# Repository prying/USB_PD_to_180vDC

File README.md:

View this project on [CADLAB.io](https://cadlab.io/project/23945). 

# USB_PD_to_180vDC
uses usb power delivery to get a higher voltage and then steps it up to 180v for nixie tubes

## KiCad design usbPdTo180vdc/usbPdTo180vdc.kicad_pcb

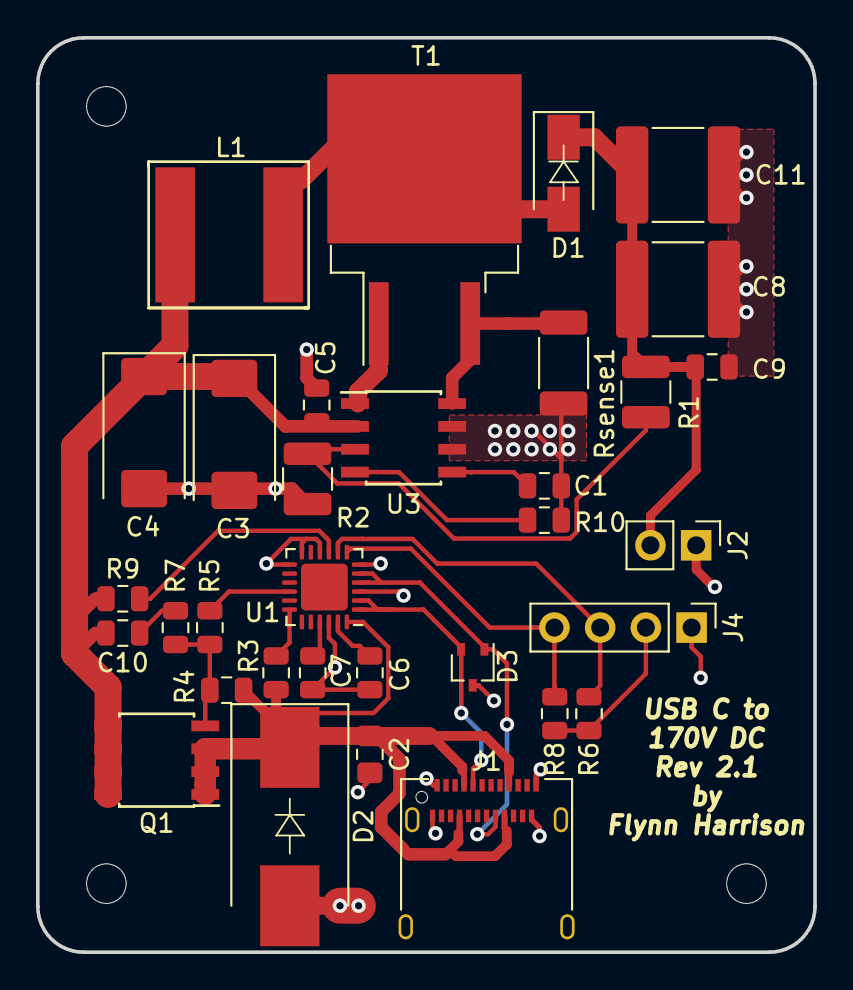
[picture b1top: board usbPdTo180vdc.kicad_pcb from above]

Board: 2 copper layers, 43.2 x 50.8 mm, 33 parts (0 on the bottom side), 22 nets.

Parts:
C1, C5, C9, C10: 0.1uF; C_0805_2012Metric
C2: 4.7uF; C_0805_2012Metric_Pad1.15x1.40mm_HandSolder
C3: 10uF; CP_EIA-7343-30_AVX-N
C4: 100uf; CP_EIA-7343-30_AVX-N
C6, C7: 1uF; C_0805_2012Metric
C8, C11: 2.2uF; C_2220_5650Metric
D1: ES2F; D_SMA
D2: SM15T; D_SMC_Handsoldering
D3: ESDA25W; SOT-323_SC-70
J1: 12401610E4_2A; USB_C_Receptacle_Amphenol_12401610E4-2A
J2: CONN_02; PinHeader_1x02_P2.54mm_Vertical
J4: QWIIC_CONNECTORJS-1MM; PinHeader_1x04_P2.54mm_Vertical
L1: 100uH; ASPI-8040S-101M-TCT-ND SMD
Q1: STS6P3LLH6; SOIC-8_3.9x4.9mm_P1.27mm
R1: 1M5; R_1210_3225Metric
R2: 12.7k; R_1210_3225Metric
R3, R9: 1K; R_0805_2012Metric
R4: 100K; R_0805_2012Metric
R5: 22K; R_0805_2012Metric
R6, R8: 2.2k; R_0805_2012Metric
R7: 100; R_0805_2012Metric
R10: 0; R_0805_2012Metric
Rsense1: 0R100; R_2010_5025Metric
T1: IRF644S; TO-263-2
U1: STUSB4500QTR; QFN-24-1EP_4x4mm_P0.5mm_EP2.6x2.6mm
U3: MAX1771ESA; SOIC-8_3.9x4.9mm_P1.27mm

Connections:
+3V3: J4.2, R6.1, R8.1
+15V: C3.1, C4.1, C5.1, C10.2, L1.1, Q1.5, Q1.6, Q1.7, Q1.8, R9.1, U3.2
GND: C1.2, C2.2, C3.2, C4.2, C5.2, C6.2, C7.2, C8.2, C9.2, C11.2, D2.2, D3.3, J1.A1, J1.A12, J1.B1, J1.B12, J2.1, J4.1, R2.2, R10.2, Rsense1.2, U1.3, U1.6, U1.10, U1.12, U1.13, U1.22, U3.6, U3.7
HV+: C8.1, C9.1, C11.1, D1.1, J2.2, R1.1
unnamed: C1.1, U3.5
unnamed: C6.1, U1.23
unnamed: C7.1, U1.21
unnamed: C10.1, R7.2
unnamed: D1.2, L1.2, T1.2
unnamed: D3.1, J1.B5, U1.4, U1.5
unnamed: D3.2, J1.A5, U1.1, U1.2
unnamed: Q1.4, R4.2, R5.1, R7.1
unnamed: R1.2, R2.1, U3.3
unnamed: R3.2, U1.18
unnamed: R5.2, U1.16
unnamed: R9.2, U1.9
unnamed: R10.1, U3.4
unnamed: Rsense1.1, T1.3, U3.8
unnamed: T1.1, U3.1
SCL: J4.4, R8.2, U1.7
SDA: J4.3, R6.2, U1.8
Vin: C2.1, D2.1, J1.A4, J1.A9, J1.B4, J1.B9, Q1.1, Q1.2, Q1.3, R3.1, R4.1, U1.24

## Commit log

2021-03-01 Backlink to CADLAB.io has been added.
